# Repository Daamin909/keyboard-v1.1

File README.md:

# Daamin's Keyboard - ShrekBoard

Made by [Daamin](https://daamin.tech)

Features:

- 78x keys!
- TKL Layout minus (9 keys above the arrow keys) and Fn moved to the bottom-left.
- 0.91" OLED for Pictures, Current - Playing Media etc
- EC11 Rotary Encoder - For Volume, Brightness etc
- Hack Club branded PCB
- Raspberry Pico USB-C replacement: [Orpheus Pico](https://orpheuspico.hackclub.com/)
- Comfy Design
- KMK firmware

## Info

I made this keyboard since I was typing a lot, and my laptop's keyboard wasn't gonna cut it. It might prove hazardous to my health over a long period, I also plan to buy a wristrest with this if it suits me.

I also think this is the perfect keyboard, since it has all the useful keys, and an RE + Display. I'll use the RE to control my songs, and the display to show the current playing song. The firmware for it is gonna be so spicy.
Oh and it also looks very nice in my eyes. Took me more than **80 hours** making the PCB, Case and researching for the BOM. I've made so many new changes and spent most of my time on revisions.

## PCB

The PCB's size is 360.4mm x 130.4mm

| Schematic                     |
| ----------------------------- |
|  |

| Front                     |
| ------------------------- |
|  |

| Back                     |
| ------------------------ |
|  |

| 3D - Front                   |
| ---------------------------- |
|  |

| 3D - Back                   |
| --------------------------- |
|  |

## Case

Thickness:-

- Top: 7mm
- Plate: 1.5mm
- Bottom: 11.5mm
- **Total**: 20mm

The case was made in Fusion360.

I chose to add branding on the bottom case only for aesthetics.
In order for the parts to be 3d printed, they're divided into 2 each.

# Top:

# Middle Plate:

# Bottom:

## 3D Render:

## Layout:

The Layout is a TKL (Tenkey-less) layout with some mods.

- removing Home, End etc island
- removing PrtSc etc island
- moving Fn key to bottom-left

## BOM

| Name                                                          | Qty | Final Price - INR (USD) | Link                                                                                                       |
| ------------------------------------------------------------- | --- | ----------------------- | ---------------------------------------------------------------------------------------------------------- |
| Gateron EF Grayish                                            | 80  | 1560 ($18.19)           | [here](https://neomacro.in/products/gateron-ef-grayish)                                                    |
| Cherry Profile PBT Keycaps                                    | 1   | 1299 ($15.14)           | [here](https://stackskb.com/store/veekos-gradient-keycaps-cherry-profile-135-keys)                         |
| Durock Smokey Screw-In Stabilizers V2 (4+1 w/ 6.25u spacebar) | 1   | 1595 ($18.6)            | [here](https://stackskb.com/store/durock-smokey-screw-in-stabilizers-v2/)                                  |
| Diode 1N4148 Through - Hole                                   | 100 | 169 ($1.97)             | [here](https://amzn.in/d/j3eLvoh)                                                                          |
| 0.91" OLED SSD1306                                            | 1   | 235 ($2.74)             | [here](https://amzn.in/d/3cISYEV)                                                                          |
| EC11 Rotary Encoder                                           | 2   | 178 ($2.08)             | [here](https://amzn.in/d/hVRxzij)                                                                          |
| M3 x 20mm Bolt                                                | 15  | 149 ($1.73)             | [here](https://amzn.in/d/8GRQWAB)                                                                          |
| M3 Nuts                                                       | 8   | 158 ($1.84)             | [here](https://amzn.in/d/7UQtsm8)                                                                          |
| M3 x 5mm Heatset Insert                                       | 25  | 179 ($2.09)             | [here](https://amzn.in/d/ixybuAc)                                                                          |
| PCB - (Black Color)                                           | 5   | 4727($55.11)            | [here](https://hc-cdn.hel1.your-objectstorage.com/s/v3/70f98601e28d2215b7cf86786f0aa80957bd7ae2_image.png) |
| Orpheus Pico                                                  | 1   | From HackClub HQ        |
| Rotary Encoder Knob                                           | 1   | From HackClub HQ        |
| Top Case - 1 (Black "./production/TOP1.step")                 | 1   | Print Legion            |
| Top Case - 2 (Black "./production/TOP2.step")                 | 1   | Print Legion            |
| Middle Plate - 1 (Black "./production/MIDDLE1.step")          | 1   | Print Legion            |
| Middle Plate - 2 (Black "./production/MIDDLE2.step")          | 1   | Print Legion            |
| Bottom Case - 1 (Black "./production/BOTTOM1.step")           | 1   | Print Legion            |
| Bottom Case - 2 (Black "./production/BOTTOM2.step")           | 1   | Print Legion            |

## Total Pricing

The keyboard comes out to be 10,249 INR ($119.49) when adding ordered parts and PCB. Does not include 3D - Printed case, Pico and Knob.
PS:- (Seed Studio costs $142 )
I have chose "air registered mail" over "UPS World Saver" because air registered mail is less likely to get customs even if it is more expensive.

## Notes :-

I want all the six 3D-printed parts to be printed in black color.
^ that includes: TOP1.step, TOP2.step, BOTTOM1.step, BOTTOM2.step, MIDDLE1.step and MIDDLE2.step
I want the 1x Rotary encoder knob as well.

Some of the above items, were ordered in packs due to unavailability of singular items.
The pricing might slightly vary due to flash sales, and dollar market trends.

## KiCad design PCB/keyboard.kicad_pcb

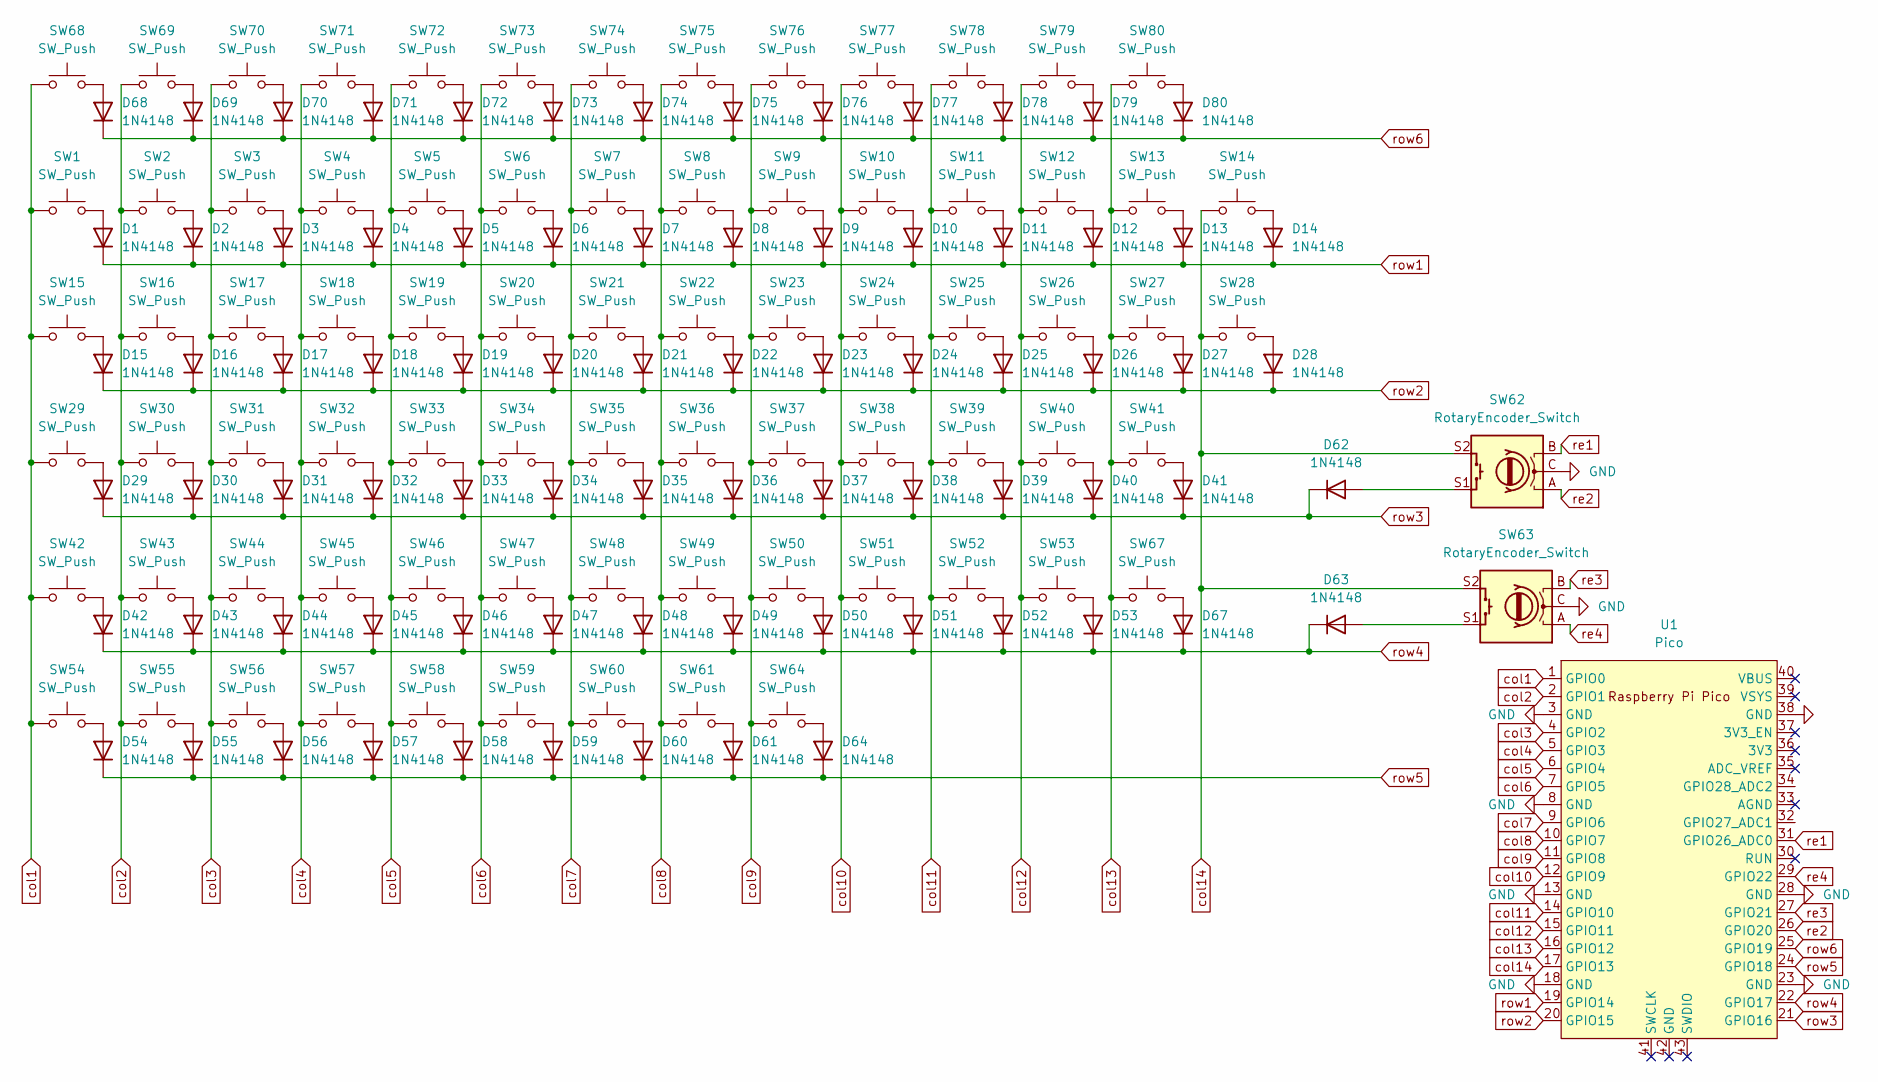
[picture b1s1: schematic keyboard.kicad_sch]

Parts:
D1, D2, D3, D4, D5, D6, D7, D8, D9, D10, D11, D12, D13, D14, D15, D16, D17, D18, D19, D20, D21, D22, D23, D24, D25, D26, D27, D28, D29, D30, D31, D32, D33, D34, D35, D36, D37, D38, D39, D40, D41, D42, D43, D44, D45, D46, D47, D48, D49, D50, D51, D52, D53, D54, D55, D56, D57, D58, D59, D60, D61, D62, D63, D64, D67, D68, D69, D70, D71, D72, D73, D74, D75, D76, D77, D78, D79, D80: 1N4148; D_DO-35_SOD27_P7.62mm_Horizontal
SW1, SW2, SW3, SW4, SW5, SW6, SW7, SW8, SW9, SW10, SW11, SW12, SW13, SW16, SW17, SW18, SW19, SW20, SW21, SW22, SW23, SW24, SW25, SW26, SW27, SW30, SW31, SW32, SW33, SW34, SW35, SW36, SW37, SW38, SW39, SW40, SW43, SW44, SW45, SW46, SW47, SW48, SW49, SW50, SW51, SW52, SW60, SW61, SW64, SW67, SW68, SW69, SW70, SW71, SW72, SW73, SW74, SW75, SW76, SW77, SW78, SW79, SW80: SW_Push; SW_Cherry_MX_1.00u_PCB
SW14: SW_Push; SW_Cherry_MX_2.00u_PCB
SW15, SW28: SW_Push; SW_Cherry_MX_1.50u_PCB
SW29, SW53: SW_Push; SW_Cherry_MX_1.75u_PCB
SW41, SW42: SW_Push; SW_Cherry_MX_2.25u_PCB
SW54, SW55, SW56, SW58, SW59: SW_Push; SW_Cherry_MX_1.25u_PCB
SW57: SW_Push; SW_Cherry_MX_6.25u_PCB
SW62, SW63: RotaryEncoder_Switch; RotaryEncoder_Alps_EC11E-Switch_Vertical_H20mm_CircularMoun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
U1: Pico; RPi_Pico_SMD_TH

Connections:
GND: SW62.C, SW63.C, U1.3 (GND), U1.8 (GND), U1.13 (GND), U1.18 (GND), U1.23 (GND), U1.28 (GND), U1.38 (GND)
unnamed: D1.2 (A), SW1.2
unnamed: D2.2 (A), SW2.2
unnamed: D3.2 (A), SW3.2
unnamed: D4.2 (A), SW4.2
unnamed: D5.2 (A), SW5.2
unnamed: D6.2 (A), SW6.2
unnamed: D7.2 (A), SW7.2
unnamed: D8.2 (A), SW8.2
unnamed: D9.2 (A), SW9.2
unnamed: D10.2 (A), SW10.2
unnamed: D11.2 (A), SW11.2
unnamed: D12.2 (A), SW12.2
unnamed: D13.2 (A), SW13.2
unnamed: D14.2 (A), SW14.2
unnamed: D15.2 (A), SW15.2
unnamed: D16.2 (A), SW16.2
unnamed: D17.2 (A), SW17.2
unnamed: D18.2 (A), SW18.2
unnamed: D19.2 (A), SW19.2
unnamed: D20.2 (A), SW20.2
unnamed: D21.2 (A), SW21.2
unnamed: D22.2 (A), SW22.2
unnamed: D23.2 (A), SW23.2
unnamed: D24.2 (A), SW24.2
unnamed: D25.2 (A), SW25.2
unnamed: D26.2 (A), SW26.2
unnamed: D27.2 (A), SW27.2
unnamed: D28.2 (A), SW28.2
unnamed: D29.2 (A), SW29.2
unnamed: D30.2 (A), SW30.2
unnamed: D31.2 (A), SW31.2
unnamed: D32.2 (A), SW32.2
unnamed: D33.2 (A), SW33.2
unnamed: D34.2 (A), SW34.2
unnamed: D35.2 (A), SW35.2
unnamed: D36.2 (A), SW36.2
unnamed: D37.2 (A), SW37.2
unnamed: D38.2 (A), SW38.2
unnamed: D39.2 (A), SW39.2
unnamed: D40.2 (A), SW40.2
unnamed: D41.2 (A), SW41.2
unnamed: D42.2 (A), SW42.2
unnamed: D43.2 (A), SW43.2
unnamed: D44.2 (A), SW44.2
unnamed: D45.2 (A), SW45.2
unnamed: D46.2 (A), SW46.2
unnamed: D47.2 (A), SW47.2
unnamed: D48.2 (A), SW48.2
unnamed: D49.2 (A), SW49.2
unnamed: D50.2 (A), SW50.2
unnamed: D51.2 (A), SW51.2
unnamed: D52.2 (A), SW52.2
unnamed: D53.2 (A), SW53.2
unnamed: D54.2 (A), SW54.2
unnamed: D55.2 (A), SW55.2
unnamed: D56.2 (A), SW56.2
unnamed: D57.2 (A), SW57.2
unnamed: D58.2 (A), SW58.2
unnamed: D59.2 (A), SW59.2
unnamed: D60.2 (A), SW60.2
unnamed: D61.2 (A), SW61.2
unnamed: D62.2 (A), SW62.S1
unnamed: D63.2 (A), SW63.S1
unnamed: D64.2 (A), SW64.2
unnamed: D67.2 (A), SW67.2
unnamed: D68.2 (A), SW68.2
unnamed: D69.2 (A), SW69.2
unnamed: D70.2 (A), SW70.2
unnamed: D71.2 (A), SW71.2
unnamed: D72.2 (A), SW72.2
unnamed: D73.2 (A), SW73.2
unnamed: D74.2 (A), SW74.2
unnamed: D75.2 (A), SW75.2
unnamed: D76.2 (A), SW76.2
unnamed: D77.2 (A), SW77.2
unnamed: D78.2 (A), SW78.2
unnamed: D79.2 (A), SW79.2
unnamed: D80.2 (A), SW80.2
col1: SW1.1, SW15.1, SW29.1, SW42.1, SW54.1, SW68.1, U1.1 (GPIO0)
col2: SW2.1, SW16.1, SW30.1, SW43.1, SW55.1, SW69.1, U1.2 (GPIO1)
col3: SW3.1, SW17.1, SW31.1, SW44.1, SW56.1, SW70.1, U1.4 (GPIO2)
col4: SW4.1, SW18.1, SW32.1, SW45.1, SW57.1, SW71.1, U1.5 (GPIO3)
col5: SW5.1, SW19.1, SW33.1, SW46.1, SW58.1, SW72.1, U1.6 (GPIO4)
col6: SW6.1, SW20.1, SW34.1, SW47.1, SW59.1, SW73.1, U1.7 (GPIO5)
col7: SW7.1, SW21.1, SW35.1, SW48.1, SW60.1, SW74.1, U1.9 (GPIO6)
col8: SW8.1, SW22.1, SW36.1, SW49.1, SW61.1, SW75.1, U1.10 (GPIO7)
col9: SW9.1, SW23.1, SW37.1, SW50.1, SW64.1, SW76.1, U1.11 (GPIO8)
col10: SW10.1, SW24.1, SW38.1, SW51.1, SW77.1, U1.12 (GPIO9)
col11: SW11.1, SW25.1, SW39.1, SW52.1, SW78.1, U1.14 (GPIO10)
col12: SW12.1, SW26.1, SW40.1, SW53.1, SW79.1, U1.15 (GPIO11)
col13: SW13.1, SW27.1, SW41.1, SW67.1, SW80.1, U1.16 (GPIO12)
col14: SW14.1, SW28.1, SW62.S2, SW63.S2, U1.17 (GPIO13)
re1: SW62.B, U1.31 (GPIO26_ADC0)
re2: SW62.A, U1.26 (GPIO20)
re3: SW63.B, U1.27 (GPIO21)
re4: SW63.A, U1.29 (GPIO22)
row1: D1.1 (K), D2.1 (K), D3.1 (K), D4.1 (K), D5.1 (K), D6.1 (K), D7.1 (K), D8.1 (K), D9.1 (K), D10.1 (K), D11.1 (K), D12.1 (K), D13.1 (K), D14.1 (K), U1.19 (GPIO14)
row2: D15.1 (K), D16.1 (K), D17.1 (K), D18.1 (K), D19.1 (K), D20.1 (K), D21.1 (K), D22.1 (K), D23.1 (K), D24.1 (K), D25.1 (K), D26.1 (K), D27.1 (K), D28.1 (K), U1.20 (GPIO15)
row3: D29.1 (K), D30.1 (K), D31.1 (K), D32.1 (K), D33.1 (K), D34.1 (K), D35.1 (K), D36.1 (K), D37.1 (K), D38.1 (K), D39.1 (K), D40.1 (K), D41.1 (K), D62.1 (K), U1.21 (GPIO16)
row4: D42.1 (K), D43.1 (K), D44.1 (K), D45.1 (K), D46.1 (K), D47.1 (K), D48.1 (K), D49.1 (K), D50.1 (K), D51.1 (K), D52.1 (K), D53.1 (K), D63.1 (K), D67.1 (K), U1.22 (GPIO17)
row5: D54.1 (K), D55.1 (K), D56.1 (K), D57.1 (K), D58.1 (K), D59.1 (K), D60.1 (K), D61.1 (K), D64.1 (K), U1.24 (GPIO18)
row6: D68.1 (K), D69.1 (K), D70.1 (K), D71.1 (K), D72.1 (K), D73.1 (K), D74.1 (K), D75.1 (K), D76.1 (K), D77.1 (K), D78.1 (K), D79.1 (K), D80.1 (K), U1.25 (GPIO19)

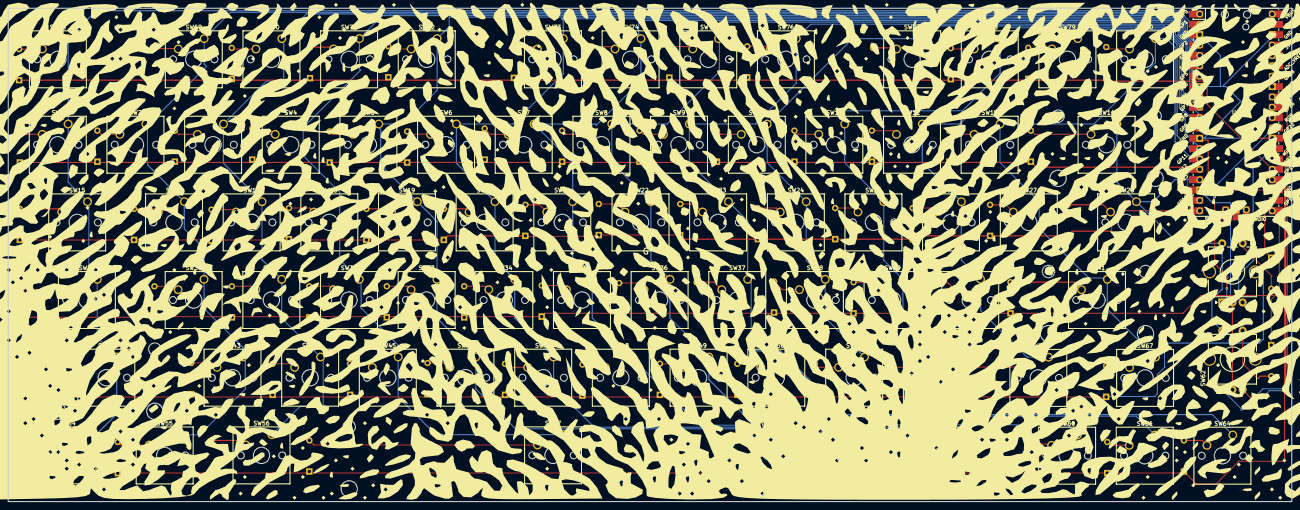
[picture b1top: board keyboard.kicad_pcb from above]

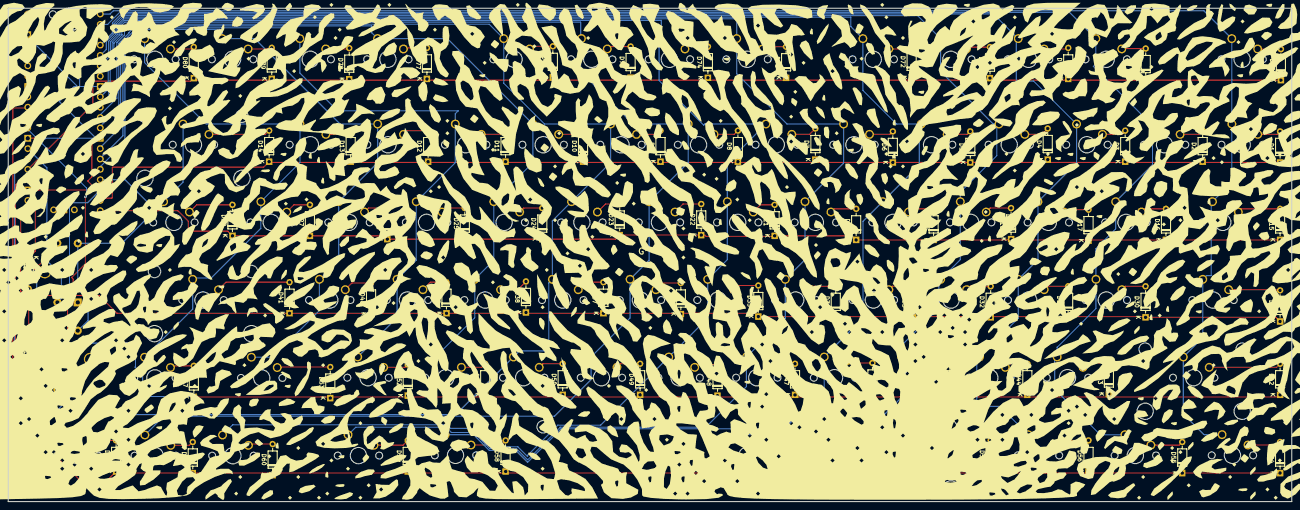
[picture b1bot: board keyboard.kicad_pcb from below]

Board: 2 copper layers, 314.9 x 121.0 mm, 157 parts (78 on the bottom side), 103 nets.

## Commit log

2025-10-14 initial commit typeshi
2025-10-14 copy PCB from v2
2025-10-15 updated PCB
